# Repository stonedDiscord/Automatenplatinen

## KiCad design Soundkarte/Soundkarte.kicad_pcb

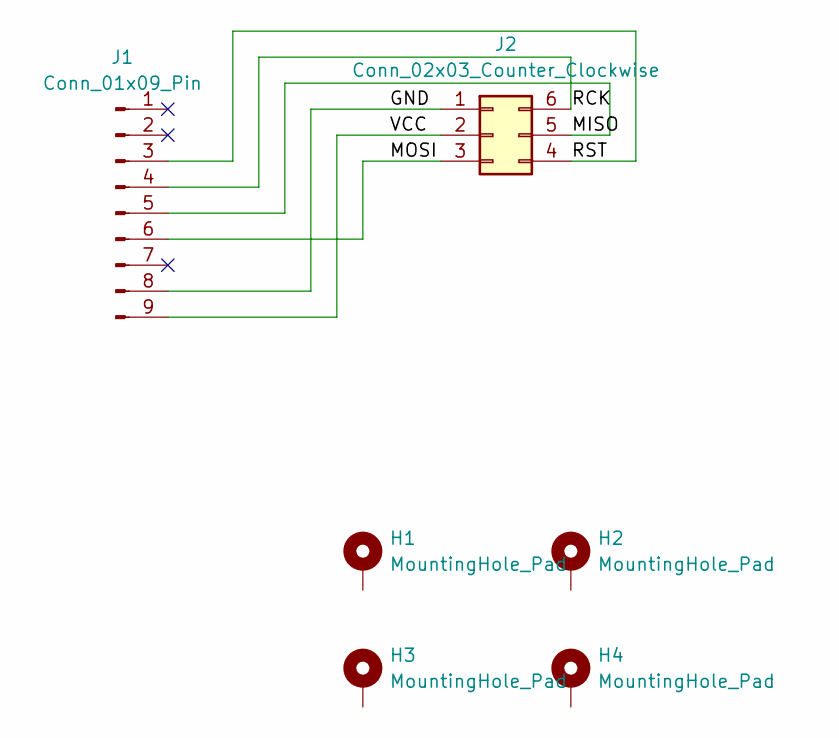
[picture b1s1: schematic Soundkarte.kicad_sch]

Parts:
H1, H2, H3, H4: MountingHole_Pad; MountingHole_4mm_Pad
J1: Conn_01x09_Pin; PinHeader_1x09_P2.54mm_Vertical
J2: Conn_02x03_Counter_Clockwise; PinHeader_2x03_P2.54mm_Vertical

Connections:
/GND: J1.8, J2.1
/MISO: J1.5, J2.5
/MOSI: J1.6, J2.3
/RCK: J1.4, J2.6
/RST: J1.3, J2.4
/VCC: J1.9, J2.2

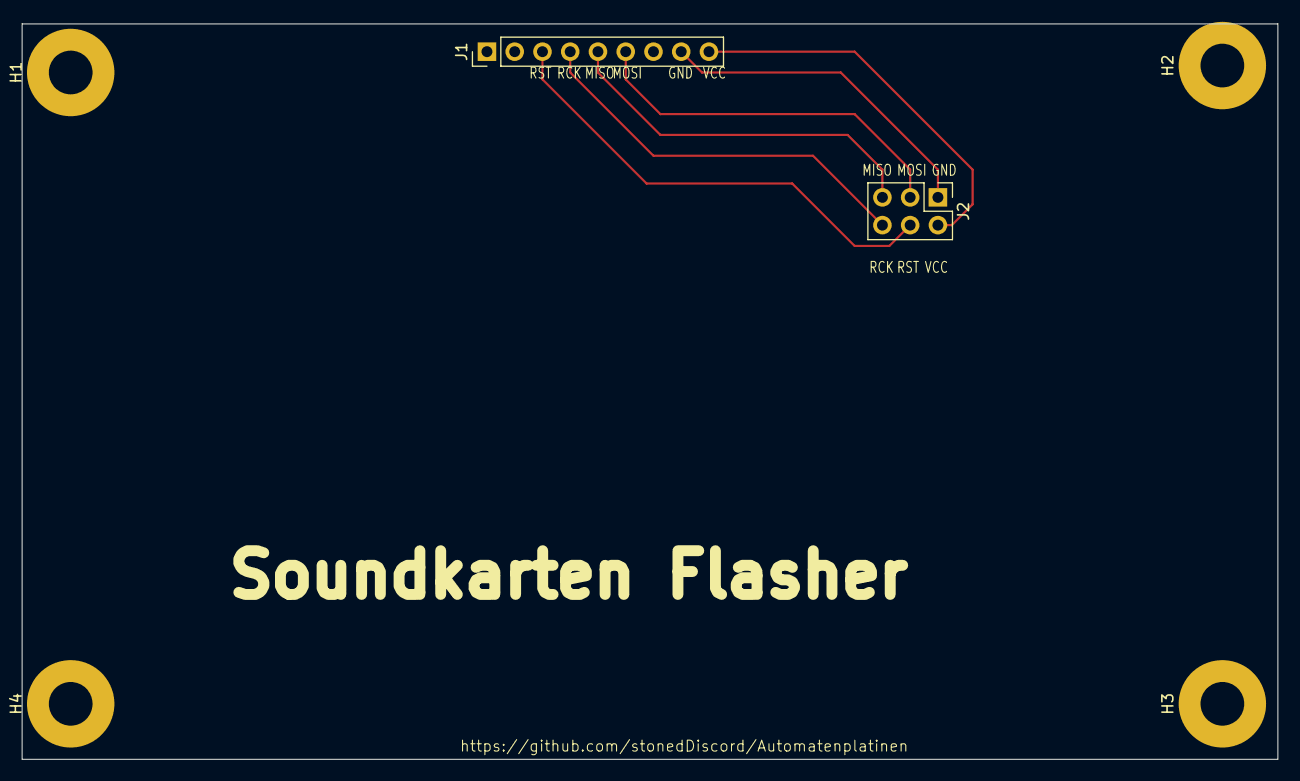
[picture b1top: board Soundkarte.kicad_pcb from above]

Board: 2 copper layers, 114.9 x 67.3 mm, 6 parts (0 on the bottom side), 6 nets.

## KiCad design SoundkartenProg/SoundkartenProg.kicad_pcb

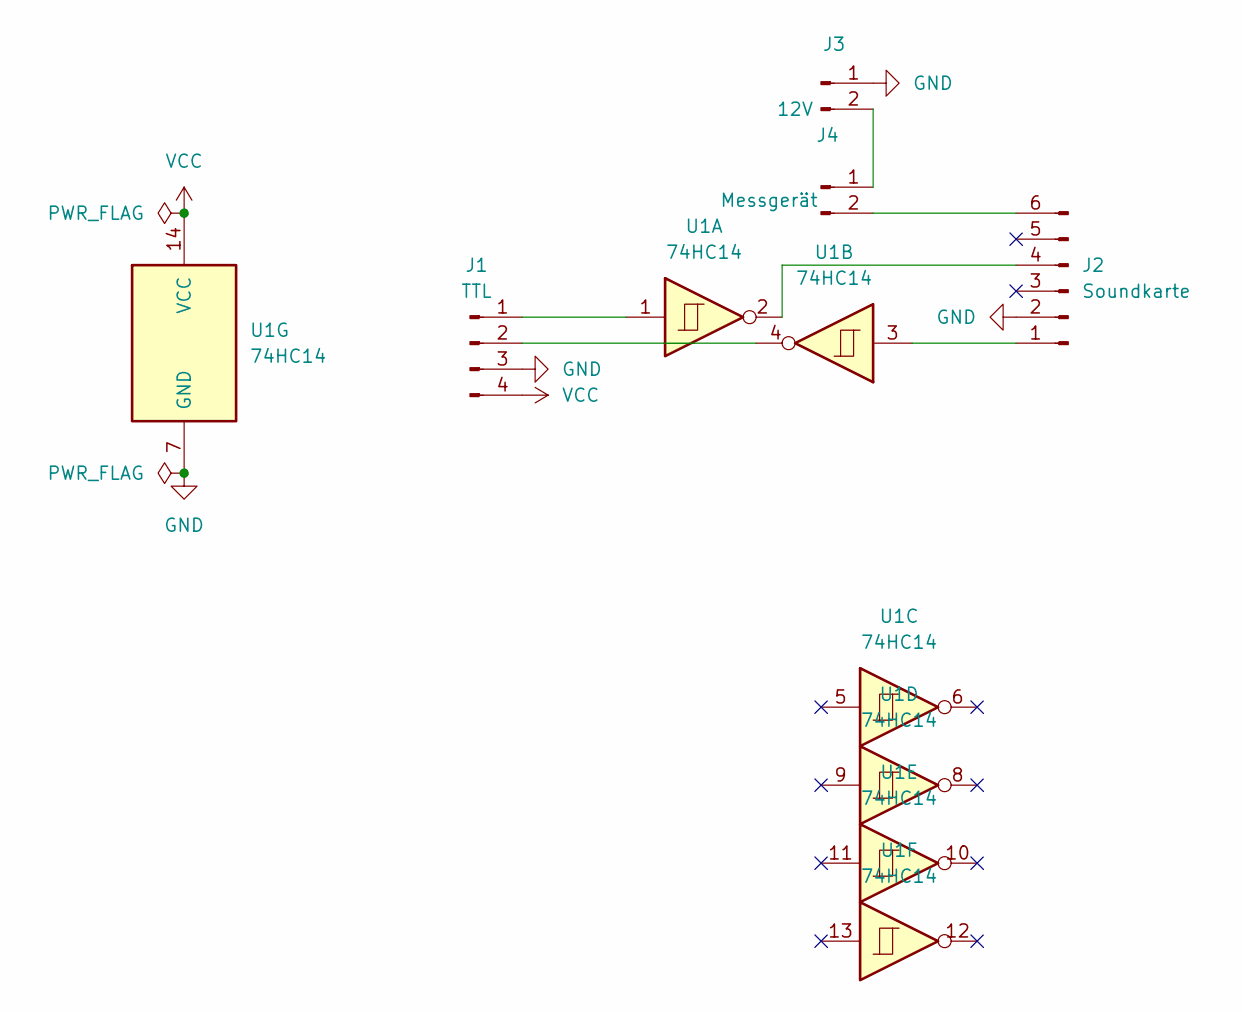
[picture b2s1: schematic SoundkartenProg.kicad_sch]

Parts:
J1: TTL; PinHeader_1x04_P2.54mm_Vertical
J2: Soundkarte; PinHeader_1x06_P2.54mm_Vertical
J3: 12V; PinHeader_1x02_P2.54mm_Vertical
J4: Messgerät; PinHeader_1x02_P2.54mm_Vertical
U1: 74HC14; SO-14_3.9x8.65mm_P1.27mm

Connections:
GND: J1.3, J2.2, J3.1, U1.7 (GND)
unnamed: J1.1, U1.1
unnamed: J1.2, U1.4
unnamed: J2.1, U1.3
unnamed: J2.4, U1.2
unnamed: J2.6, J4.2
unnamed: J3.2, J4.1
VCC: J1.4, U1.14 (VCC)

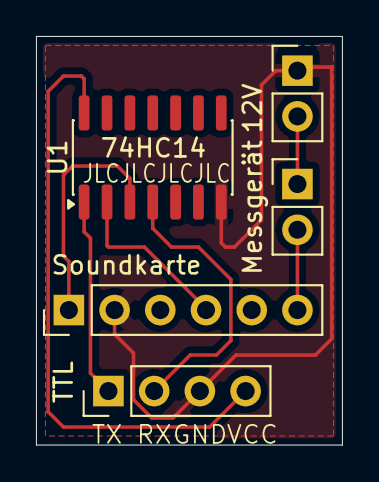
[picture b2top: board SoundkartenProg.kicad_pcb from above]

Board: 2 copper layers, 17.0 x 22.7 mm, 5 parts (0 on the bottom side), 8 nets.

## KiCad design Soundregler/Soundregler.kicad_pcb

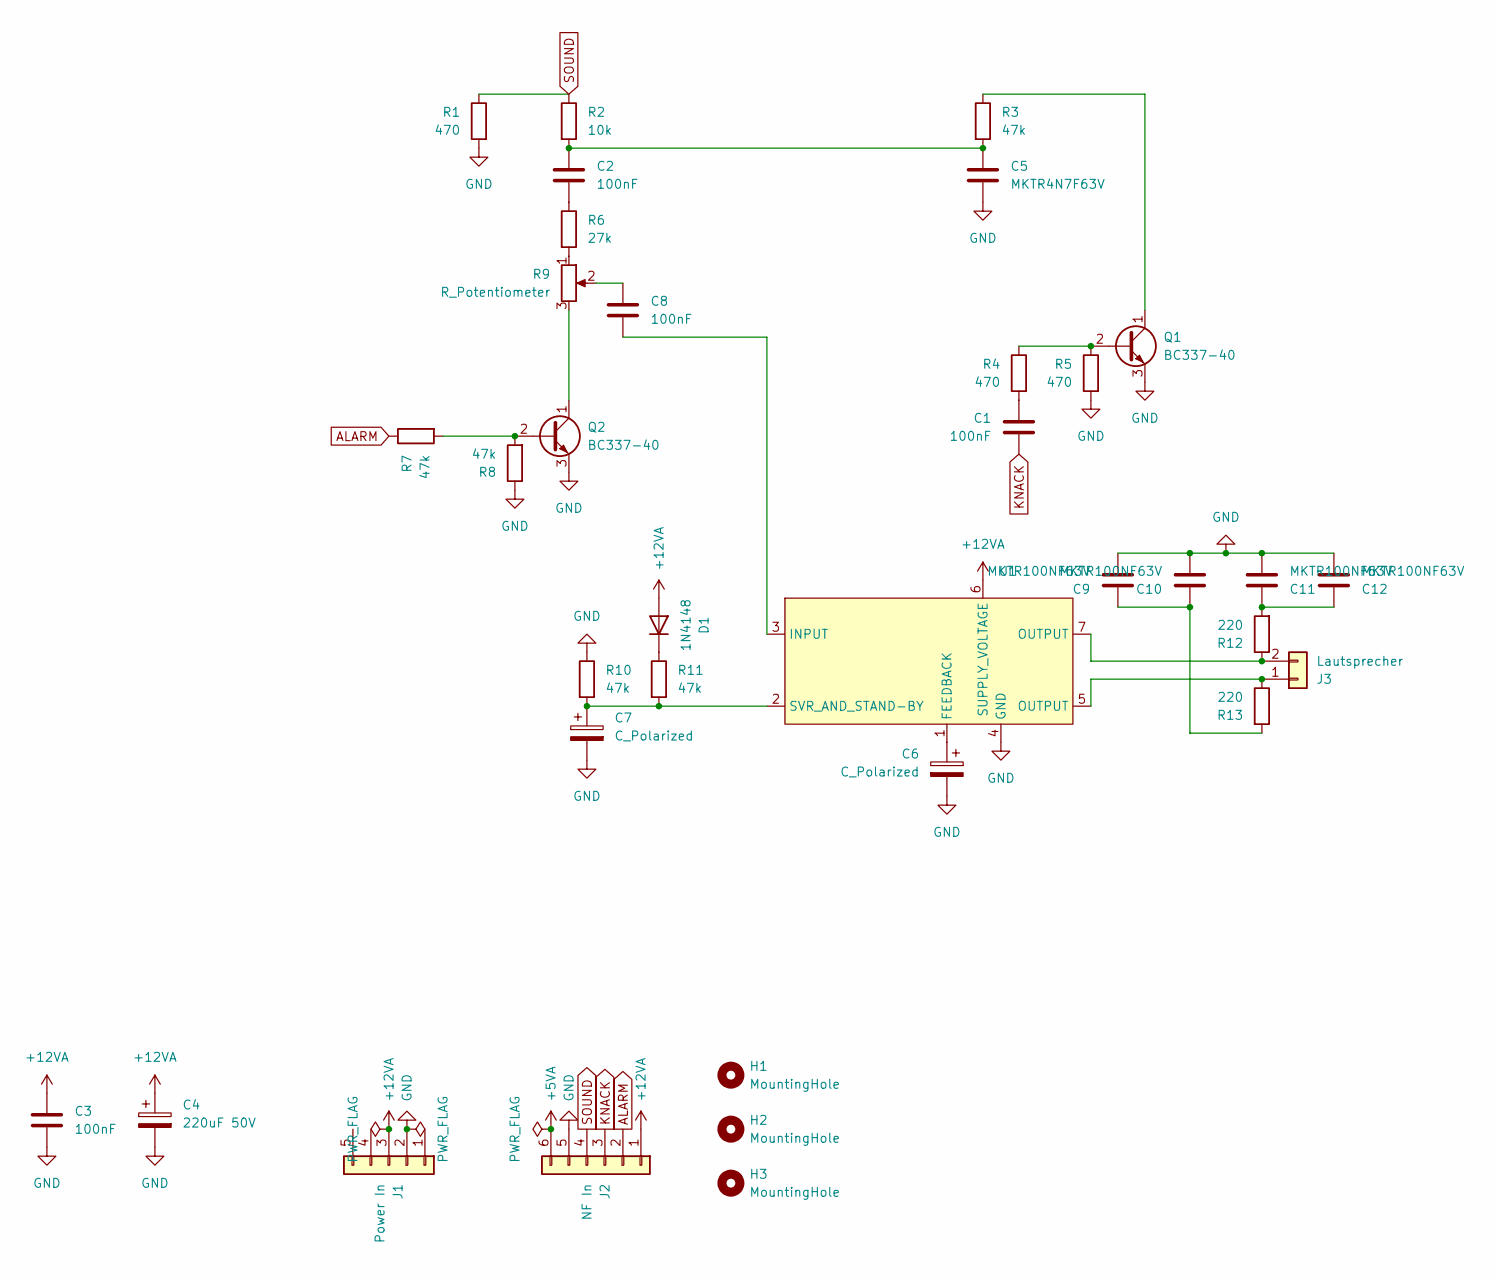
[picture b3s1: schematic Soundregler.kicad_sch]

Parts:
C1, C2, C3, C8: 100nF; C_Axial_L3.8mm_D2.6mm_P7.50mm_Horizontal
C4: 220uF 50V; CP_Radial_D8.0mm_P5.00mm
C5: MKTR4N7F63V; C_Rect_L7.0mm_W2.0mm_P5.00mm
C6, C7: C_Polarized; CP_Axial_L11.0mm_D5.0mm_P18.00mm_Horizontal
C9, C10, C11, C12: MKTR100NF63V; C_Rect_L7.0mm_W2.0mm_P5.00mm
D1: 1N4148; D_DO-35_SOD27_P7.62mm_Horizontal
H1, H2, H3: MountingHole; MountingHole_4.3mm_M4
J1: Power In; PinHeader_1x05_P2.54mm_Vertical
J2: NF In; PinHeader_1x06_P2.54mm_Vertical
J3: Lautsprecher; PinHeader_1x02_P2.54mm_Vertical
Q1, Q2: BC337-40; TO-92
R1, R4, R5: 470; R_Axial_DIN0207_L6.3mm_D2.5mm_P10.16mm_Horizontal
R2: 10k; R_Axial_DIN0207_L6.3mm_D2.5mm_P10.16mm_Horizontal
R3, R7, R8, R10, R11: 47k; R_Axial_DIN0207_L6.3mm_D2.5mm_P10.16mm_Horizontal
R6: 27k; R_Axial_DIN0207_L6.3mm_D2.5mm_P10.16mm_Horizontal
R9: R_Potentiometer; Potentiometer_ACP_CA9-V10_Vertical
R12, R13: 220; R_Axial_DIN0207_L6.3mm_D2.5mm_P10.16mm_Horizontal
U1: TO-220-7_P2.54x3.8mm_StaggerOdd_Lead5.85mm_TabDown

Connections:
+5VA: J2.6
+12VA: C3.1, C4.1, D1.2 (A), J1.3, J2.1, U1.6 (SUPPLY_VOLTAGE)
ALARM: J2.2, R7.1
GND: C3.2, C4.2, C5.2, C6.2, C7.2, C9.2, C10.2, C11.2, C12.2, J1.2, J2.5, Q1.3 (E), Q2.3 (E), R1.2, R5.2, R8.1, R10.1, U1.4 (GND)
KNACK: C1.1, J2.3
unnamed: C1.2, R4.2
unnamed: C2.1, R6.1
unnamed: C2.2, C5.1, R2.2, R3.2
unnamed: C8.1, R9.2
unnamed: C9.1, C10.1, R13.2
unnamed: C11.1, C12.1, R12.2
unnamed: D1.1 (K), R11.1
unnamed: J3.1, R13.1, U1.5 (OUTPUT)
unnamed: J3.2, R12.1, U1.7 (OUTPUT)
unnamed: Q1.2 (B), R4.1, R5.1
unnamed: Q1.1 (C), R3.1
unnamed: Q2.2 (B), R7.2, R8.2
unnamed: Q2.1 (C), R9.3
unnamed: R6.2, R9.1
unnamed: C6.1, U1.1 (FEEDBACK)
unnamed: C8.2, U1.3 (INPUT)
unnamed: C7.1, R10.2, R11.2, U1.2 (SVR_AND_STAND-BY)
SOUND: J2.4, R1.1, R2.1

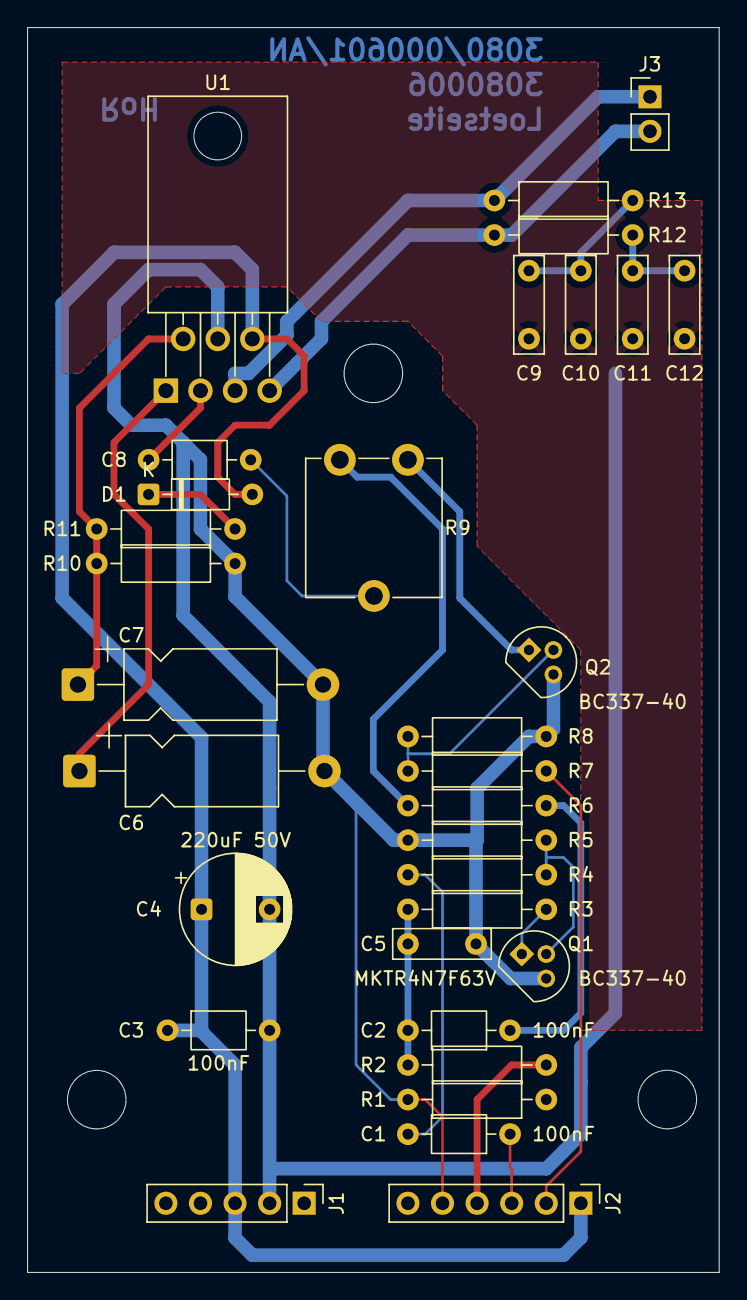
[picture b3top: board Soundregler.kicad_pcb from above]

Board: 2 copper layers, 50.8 x 91.4 mm, 35 parts (0 on the bottom side), 22 nets.

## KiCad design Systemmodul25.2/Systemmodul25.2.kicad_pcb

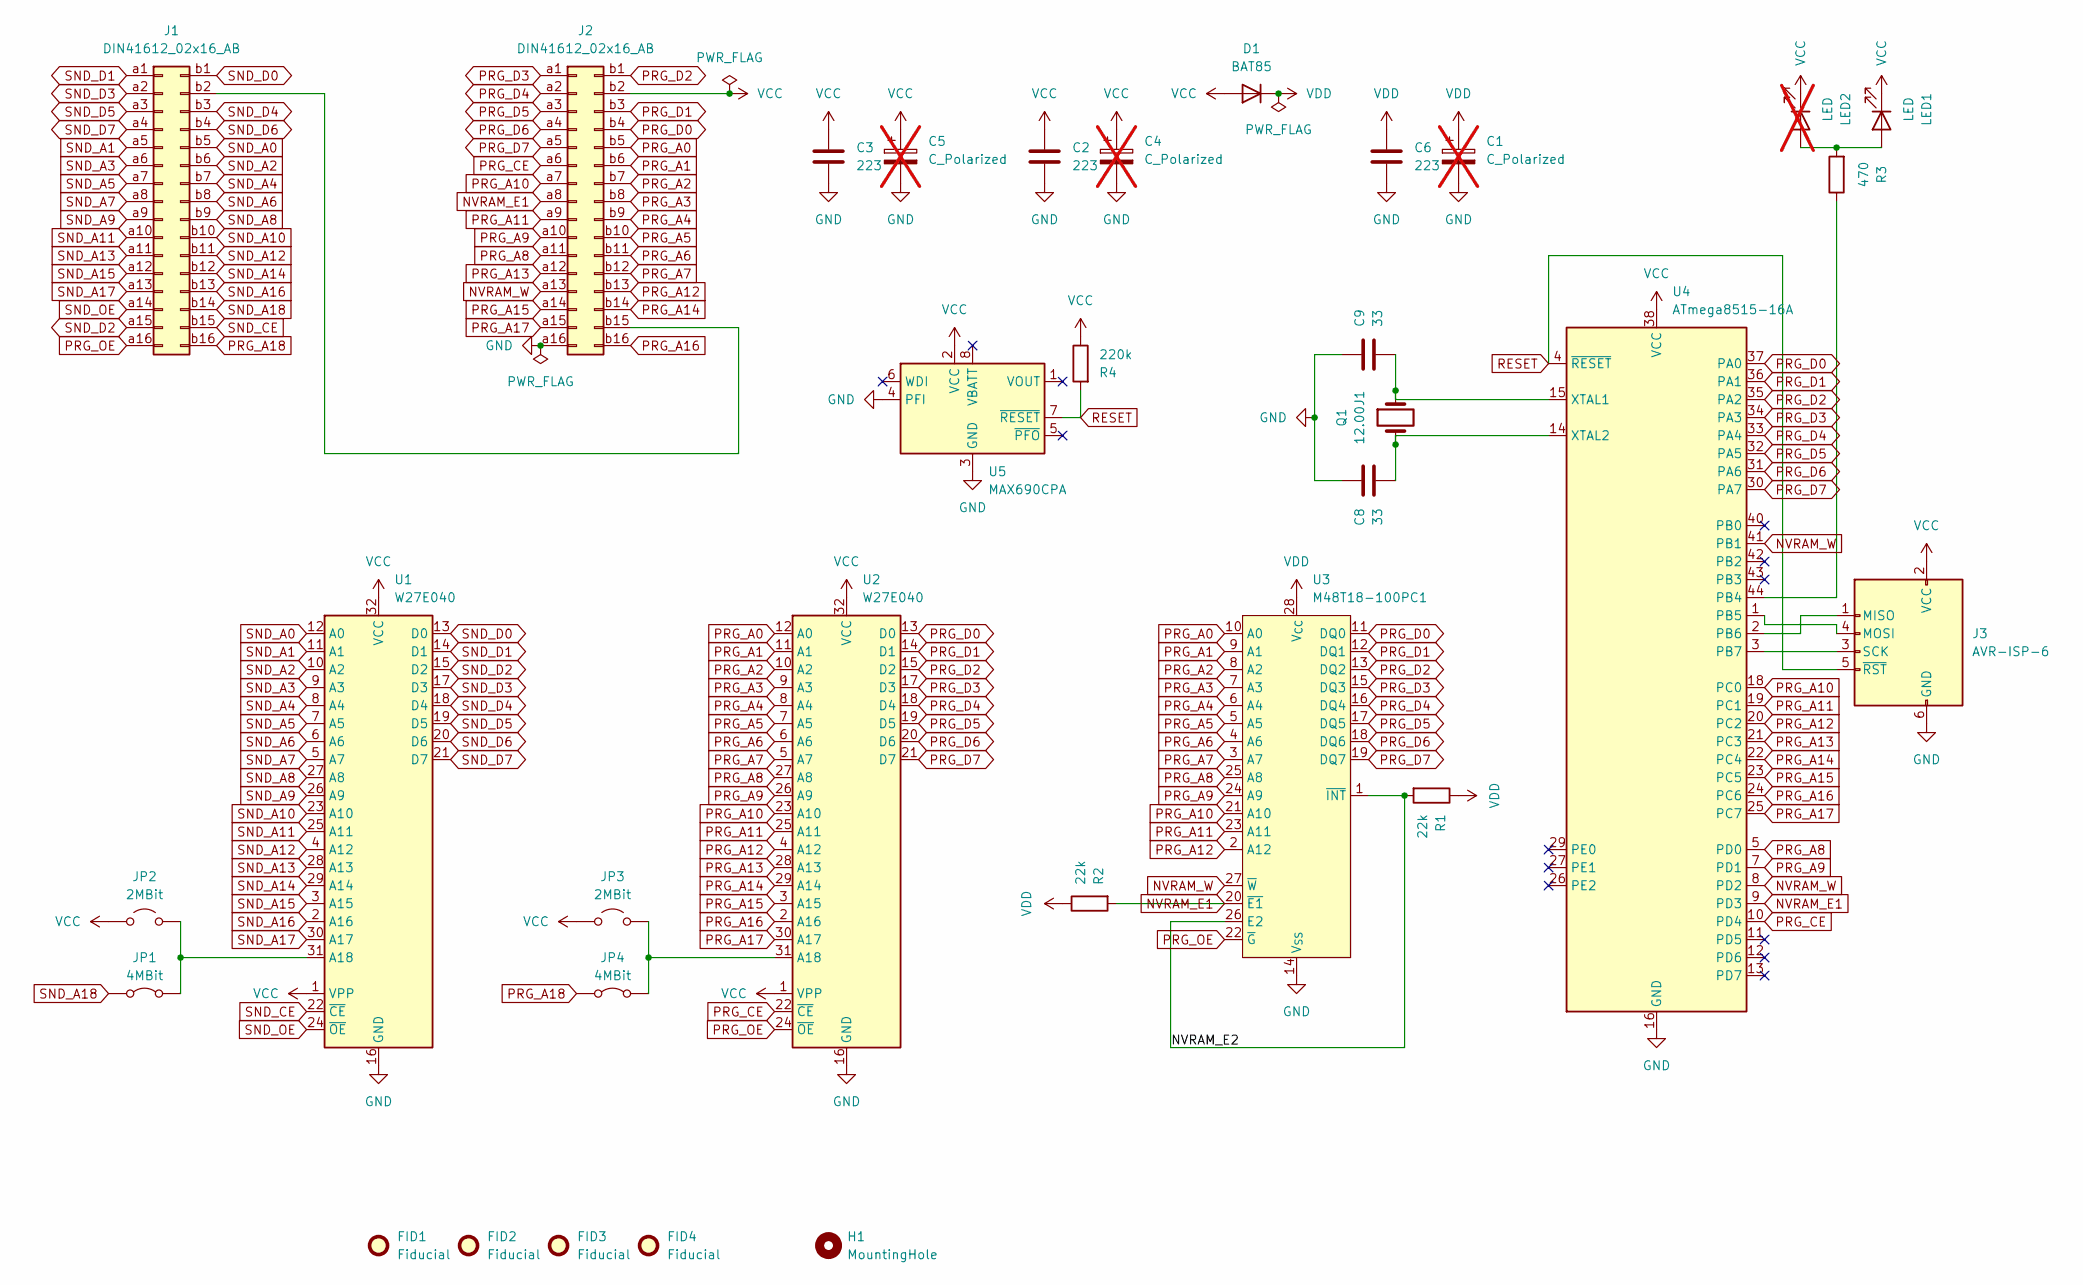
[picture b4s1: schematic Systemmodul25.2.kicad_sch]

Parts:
C1: C_Polarized; CP_Radial_Tantal_D7.0mm_P5.00mm; not fitted
C2, C3, C6: 223; C_Disc_D4.3mm_W1.9mm_P5.00mm
C4, C5: C_Polarized; CP_Radial_Tantal_D5.0mm_P5.00mm; not fitted
C8, C9: 33; C_Disc_D4.3mm_W1.9mm_P5.00mm
D1: BAT85; D_A-405_P10.16mm_Horizontal
FID1, FID2: Fiducial; Fiducial_Cross_1.5mm_Mask2mm
FID3: Fiducial; Fiducial_0.75mm_Mask1.5mm
FID4: Fiducial; Fiducial_0.5mm_Mask1mm
H1: MountingHole; MountingHole_4.3mm_M4
J1, J2: DIN41612_02x16_AB; DIN41612_Q2_2x16_Male_Vertical_THT
J3: AVR-ISP-6; IDC-Header_2x03_P2.54mm_Vertical
JP1, JP4: 4MBit; NSM_Jumper
JP2, JP3: 2MBit; NSM_Jumper
LED1: LED; LED_D5.0mm_Horizontal_O1.27mm_Z3.0mm
LED2: LED; LED_1206_3216Metric; not fitted
Q1: 12.00J1; Crystal_HC18-U_Vertical
R1, R2: 22k; R_Axial_DIN0207_L6.3mm_D2.5mm_P10.16mm_Horizontal
R3: 470; R_Axial_DIN0207_L6.3mm_D2.5mm_P10.16mm_Horizontal
R4: 220k; R_Axial_DIN0207_L6.3mm_D2.5mm_P10.16mm_Horizontal
U1, U2: W27E040; DIP-32_W15.24mm_Socket
U3: M48T18-100PC1; DIP-28_W15.24mm
U4: ATmega8515-16A; TQFP-44_10x10mm_P0.8mm
U5: MAX690CPA; DIP-8_W7.62mm

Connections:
/NVRAM_E2: R1.2, U3.1 (~INT), U3.26 (E2)
GND: C1.2, C2.2, C3.2, C4.2, C5.2, C6.2, C8.1, C9.1, J2.a16, J3.6 (GND), U1.16 (GND), U2.16 (GND), U3.14 (V_{SS}), U4.16 (GND), U5.3 (GND), U5.4 (PFI)
NVRAM_E1: J2.a8, R2.2, U3.20 (~E1), U4.9 (PD3)
NVRAM_W: J2.a13, U3.27 (~W), U4.8 (PD2), U4.41 (PB1)
unnamed: J1.b2, J2.b15
unnamed: J3.1 (MISO), U4.2 (PB6)
unnamed: J3.4 (MOSI), U4.1 (PB5)
unnamed: J3.3 (SCK), U4.3 (PB7)
unnamed: JP1.1 (A), JP2.1 (A), U1.31 (A18)
unnamed: JP3.1 (A), JP4.1 (A), U2.31 (A18)
unnamed: LED1.2 (A), LED2.2 (A), R3.2
unnamed: R3.1, U4.44 (PB4)
unnamed: C9.2, Q1.1, U4.15 (XTAL1)
unnamed: C8.2, Q1.2, U4.14 (XTAL2)
PRG_A0: J2.b5, U2.12 (A0), U3.10 (A0)
PRG_A1: J2.b6, U2.11 (A1), U3.9 (A1)
PRG_A2: J2.b7, U2.10 (A2), U3.8 (A2)
PRG_A3: J2.b8, U2.9 (A3), U3.7 (A3)
PRG_A4: J2.b9, U2.8 (A4), U3.6 (A4)
PRG_A5: J2.b10, U2.7 (A5), U3.5 (A5)
PRG_A6: J2.b11, U2.6 (A6), U3.4 (A6)
PRG_A7: J2.b12, U2.5 (A7), U3.3 (A7)
PRG_A8: J2.a11, U2.27 (A8), U3.25 (A8), U4.5 (PD0)
PRG_A9: J2.a10, U2.26 (A9), U3.24 (A9), U4.7 (PD1)
PRG_A10: J2.a7, U2.23 (A10), U3.21 (A10), U4.18 (PC0)
PRG_A11: J2.a9, U2.25 (A11), U3.23 (A11), U4.19 (PC1)
PRG_A12: J2.b13, U2.4 (A12), U3.2 (A12), U4.20 (PC2)
PRG_A13: J2.a12, U2.28 (A13), U4.21 (PC3)
PRG_A14: J2.b14, U2.29 (A14), U4.22 (PC4)
PRG_A15: J2.a14, U2.3 (A15), U4.23 (PC5)
PRG_A16: J2.b16, U2.2 (A16), U4.24 (PC6)
PRG_A17: J2.a15, U2.30 (A17), U4.25 (PC7)
PRG_A18: J1.b16, JP4.2 (B)
PRG_CE: J2.a6, U2.22 (~CE), U4.10 (PD4)
PRG_D0: J2.b4, U2.13 (D0), U3.11 (DQ0), U4.37 (PA0)
PRG_D1: J2.b3, U2.14 (D1), U3.12 (DQ1), U4.36 (PA1)
PRG_D2: J2.b1, U2.15 (D2), U3.13 (DQ2), U4.35 (PA2)
PRG_D3: J2.a1, U2.17 (D3), U3.15 (DQ3), U4.34 (PA3)
PRG_D4: J2.a2, U2.18 (D4), U3.16 (DQ4), U4.33 (PA4)
PRG_D5: J2.a3, U2.19 (D5), U3.17 (DQ5), U4.32 (PA5)
PRG_D6: J2.a4, U2.20 (D6), U3.18 (DQ6), U4.31 (PA6)
PRG_D7: J2.a5, U2.21 (D7), U3.19 (DQ7), U4.30 (PA7)
PRG_OE: J1.a16, U2.24 (~OE), U3.22 (~G)
RESET: J3.5 (~RST), R4.2, U4.4 (~RESET), U5.7 (~RESET)
SND_A0: J1.b5, U1.12 (A0)
SND_A1: J1.a5, U1.11 (A1)
SND_A2: J1.b6, U1.10 (A2)
SND_A3: J1.a6, U1.9 (A3)
SND_A4: J1.b7, U1.8 (A4)
SND_A5: J1.a7, U1.7 (A5)
SND_A6: J1.b8, U1.6 (A6)
SND_A7: J1.a8, U1.5 (A7)
SND_A8: J1.b9, U1.27 (A8)
SND_A9: J1.a9, U1.26 (A9)
SND_A10: J1.b10, U1.23 (A10)
SND_A11: J1.a10, U1.25 (A11)
SND_A12: J1.b11, U1.4 (A12)
SND_A13: J1.a11, U1.28 (A13)
SND_A14: J1.b12, U1.29 (A14)
SND_A15: J1.a12, U1.3 (A15)
SND_A16: J1.b13, U1.2 (A16)
SND_A17: J1.a13, U1.30 (A17)
SND_A18: J1.b14, JP1.2 (B)
SND_CE: J1.b15, U1.22 (~CE)
SND_D0: J1.b1, U1.13 (D0)
SND_D1: J1.a1, U1.14 (D1)
SND_D2: J1.a15, U1.15 (D2)
SND_D3: J1.a2, U1.17 (D3)
SND_D4: J1.b3, U1.18 (D4)
SND_D5: J1.a3, U1.19 (D5)
SND_D6: J1.b4, U1.20 (D6)
SND_D7: J1.a4, U1.21 (D7)
SND_OE: J1.a14, U1.24 (~OE)
VCC: C2.1, C3.1, C4.1, C5.1, D1.2 (A), J2.b2, J3.2 (VCC), JP2.2 (B), JP3.2 (B), LED1.1 (K), LED2.1 (K), R4.1, U1.1 (VPP), U1.32 (VCC), U2.1 (VPP), U2.32 (VCC), U4.38 (VCC), U5.2 (VCC)
VDD: C1.1, C6.1, D1.1 (K), R1.1, R2.1, U3.28 (V_{CC})

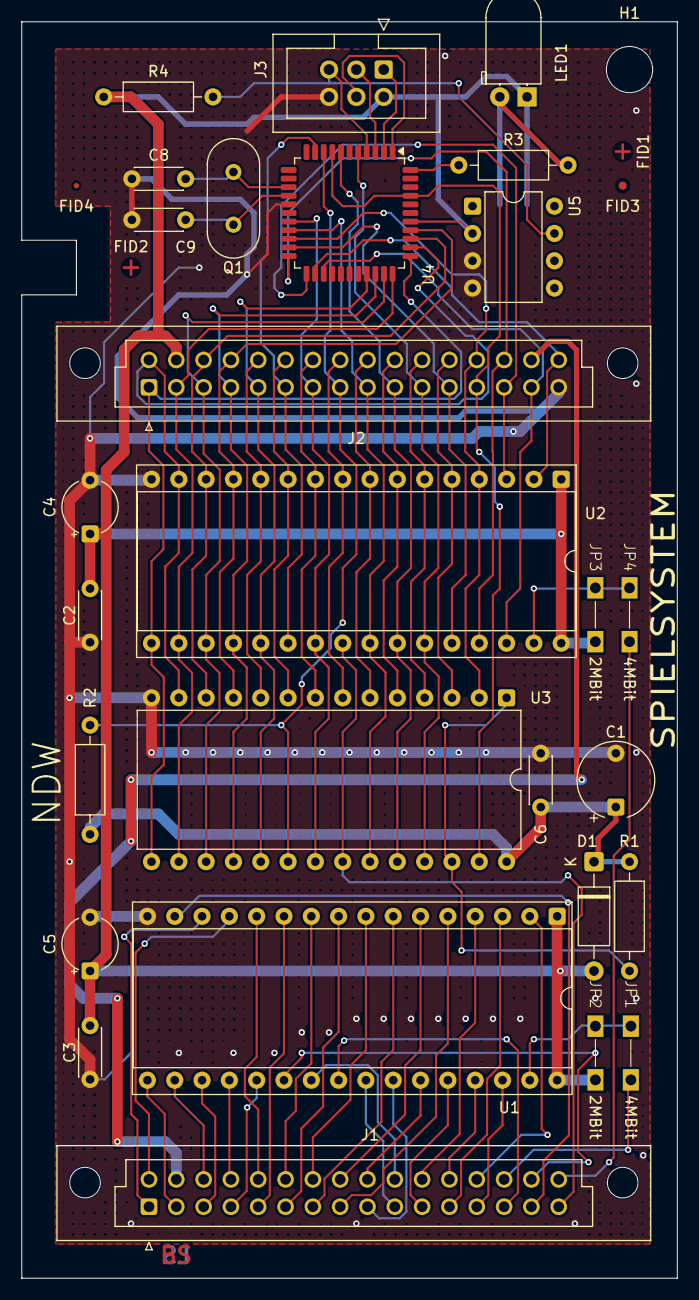
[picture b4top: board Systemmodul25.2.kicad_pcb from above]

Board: 2 copper layers, 61.0 x 116.8 mm, 33 parts (1 on the bottom side), 75 nets.

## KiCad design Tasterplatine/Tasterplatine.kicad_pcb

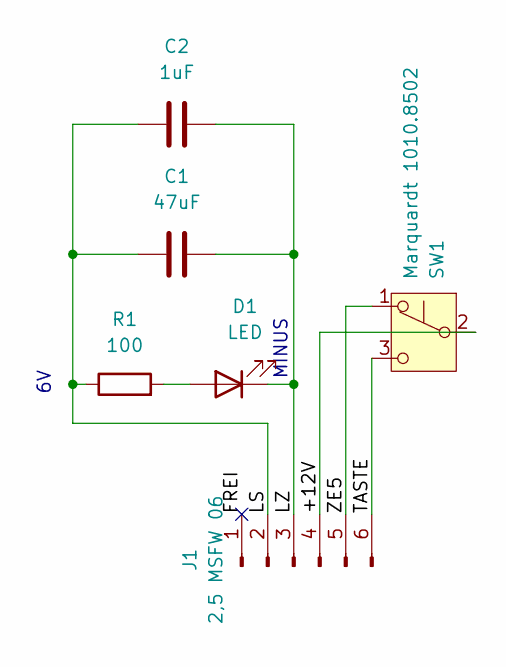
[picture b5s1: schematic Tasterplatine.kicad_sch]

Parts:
C1: 47uF; CP_EIA-3528-12_Kemet-T
C2: 1uF; C_1206_3216Metric
D1: LED; LED_PLCC_2835_Handsoldering
J1: 2,5 MSFW 06; JST_EH_S6B-EH_1x06_P2.50mm_Horizontal
R1: 100; R_1206_3216Metric
SW1: Marquardt 1010.8502; Marquardt1010

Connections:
/+12V: J1.4, SW1.2 (B)
/FREI: J1.1
/LS: C1.1, C2.1, J1.2, R1.1
/LZ: C1.2, C2.2, D1.1 (K), J1.3
/TASTE: J1.6, SW1.3 (C)
/ZE5: J1.5, SW1.1 (A)
unnamed: D1.2 (A), R1.2

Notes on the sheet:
MINUS

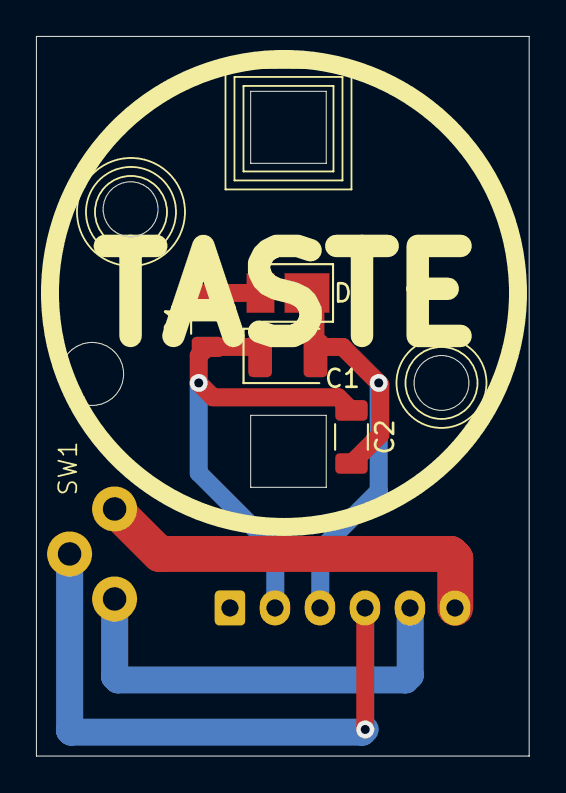
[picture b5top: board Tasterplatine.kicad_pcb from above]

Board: 2 copper layers, 27.4 x 40.0 mm, 6 parts (1 on the bottom side), 6 nets.

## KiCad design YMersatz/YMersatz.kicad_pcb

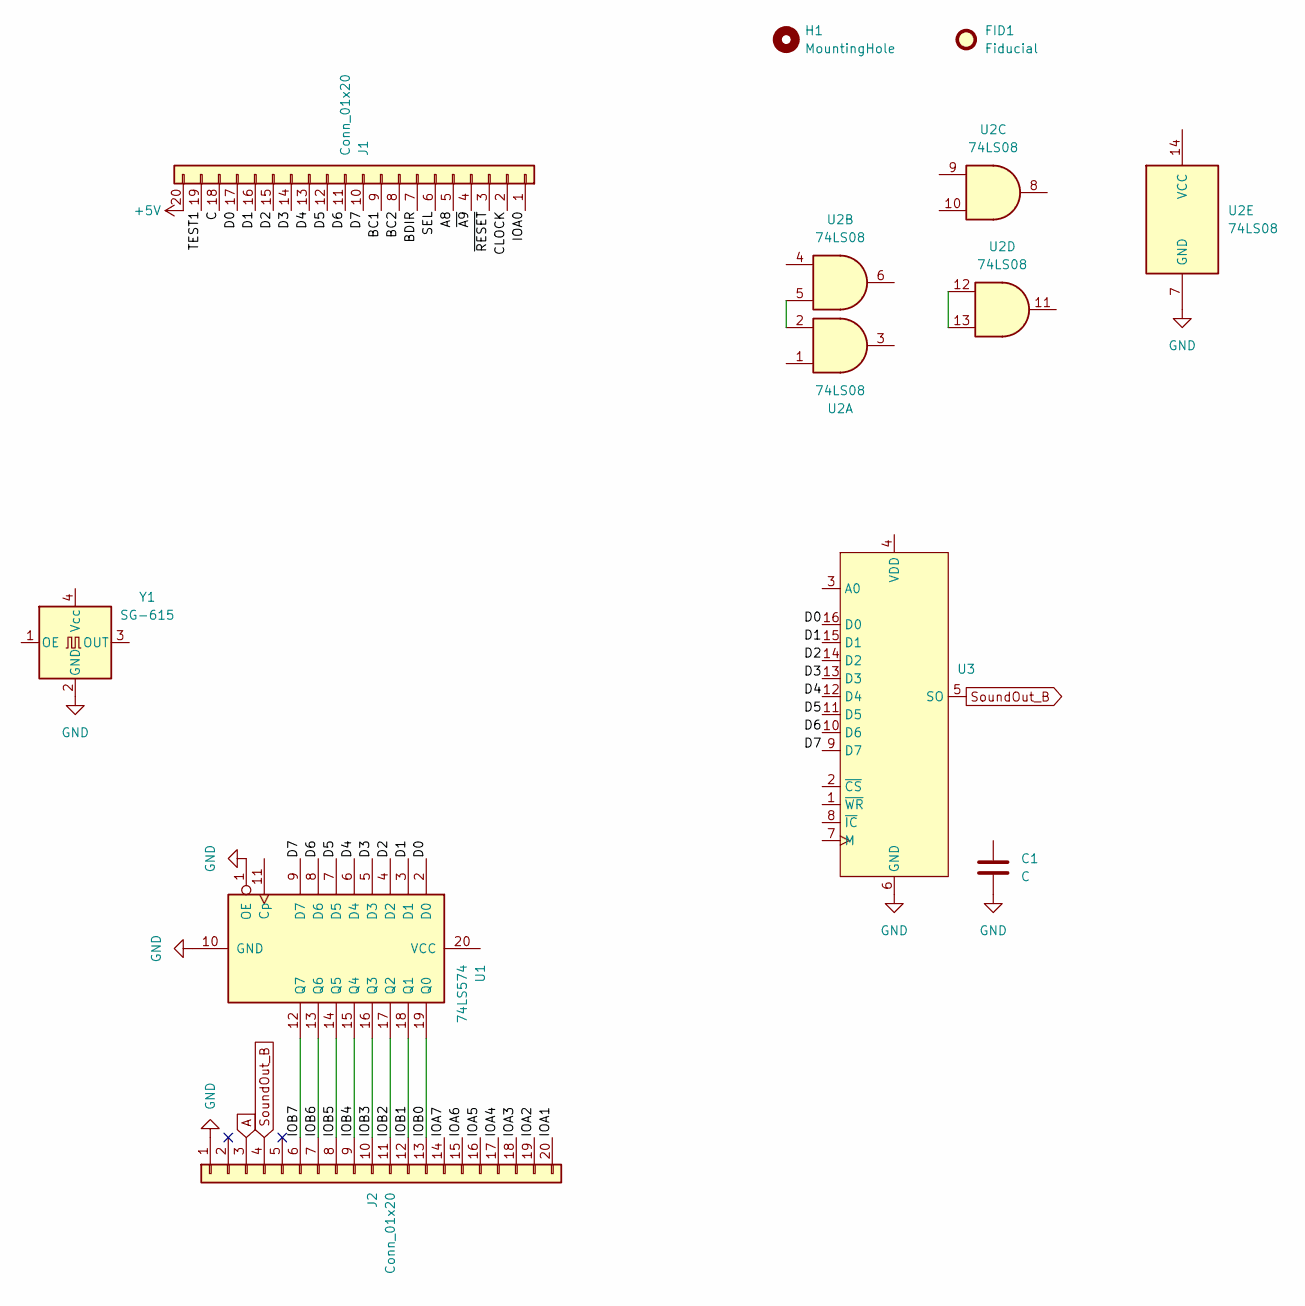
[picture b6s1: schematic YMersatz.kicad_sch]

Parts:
C1: C; C_0805_2012Metric
FID1: Fiducial; Fiducial_1.5mm_Mask3mm
H1: MountingHole; MountingHole_2.1mm
J1, J2: Conn_01x20; PinHeader_1x20_P2.54mm_Vertical
U1: 74LS574; SO-20_12.8x7.5mm_P1.27mm
U2: 74LS08; SO-14_3.9x8.65mm_P1.27mm
U3: SO-16_5.3x10.2mm_P1.27mm
Y1: SG-615; Oscillator_SMD_SeikoEpson_SG8002JA-4Pin_14.0x8.7mm

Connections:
+5V: J1.20
/A8: J1.5
/BC1: J1.9
/BC2: J1.8
/BDIR: J1.7
/C: J1.18
/CLOCK: J1.2
/D0: J1.17, U1.2 (D0), U3.16 (D0)
/D1: J1.16, U1.3 (D1), U3.15 (D1)
/D2: J1.15, U1.4 (D2), U3.14 (D2)
/D3: J1.14, U1.5 (D3), U3.13 (D3)
/D4: J1.13, U1.6 (D4), U3.12 (D4)
/D5: J1.12, U1.7 (D5), U3.11 (D5)
/D6: J1.11, U1.8 (D6), U3.10 (D6)
/D7: J1.10, U1.9 (D7), U3.9 (D7)
/IOA0: J1.1
/IOA1: J2.20
/IOA2: J2.19
/IOA3: J2.18
/IOA4: J2.17
/IOA5: J2.16
/IOA6: J2.15
/IOA7: J2.14
/IOB0: J2.13, U1.19 (Q0)
/IOB1: J2.12, U1.18 (Q1)
/IOB2: J2.11, U1.17 (Q2)
/IOB3: J2.10, U1.16 (Q3)
/IOB4: J2.9, U1.15 (Q4)
/IOB5: J2.8, U1.14 (Q5)
/IOB6: J2.7, U1.13 (Q6)
/IOB7: J2.6, U1.12 (Q7)
/SEL: J1.6
/TEST1: J1.19
/~A9: J1.4
/~RESET: J1.3
A: J2.3
GND: C1.2, J2.1, U1.1 (OE), U1.10 (GND), U2.7 (GND_7), U3.6 (GND), Y1.2 (GND_2)
unnamed: U2.2, U2.5
unnamed: U2.12, U2.13
SoundOut_B: J2.4, U3.5 (SO)

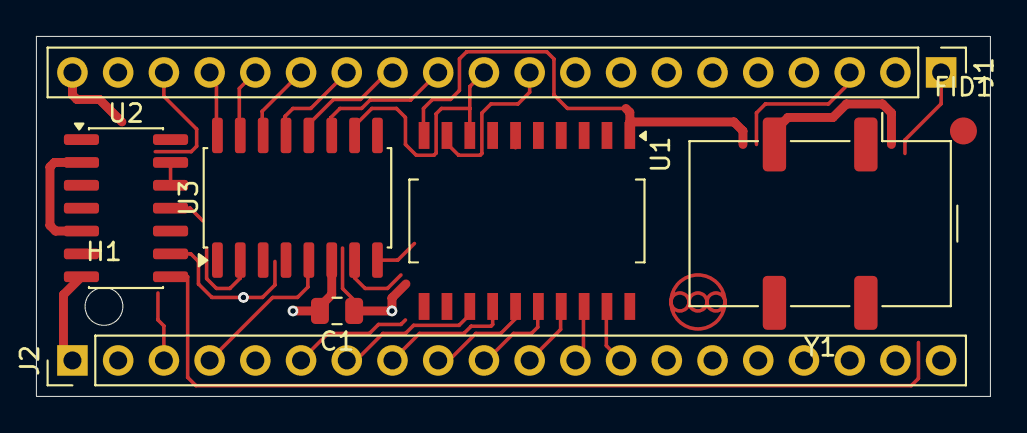
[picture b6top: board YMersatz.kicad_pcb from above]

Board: 2 copper layers, 53.0 x 20.0 mm, 9 parts (0 on the bottom side), 20 nets.

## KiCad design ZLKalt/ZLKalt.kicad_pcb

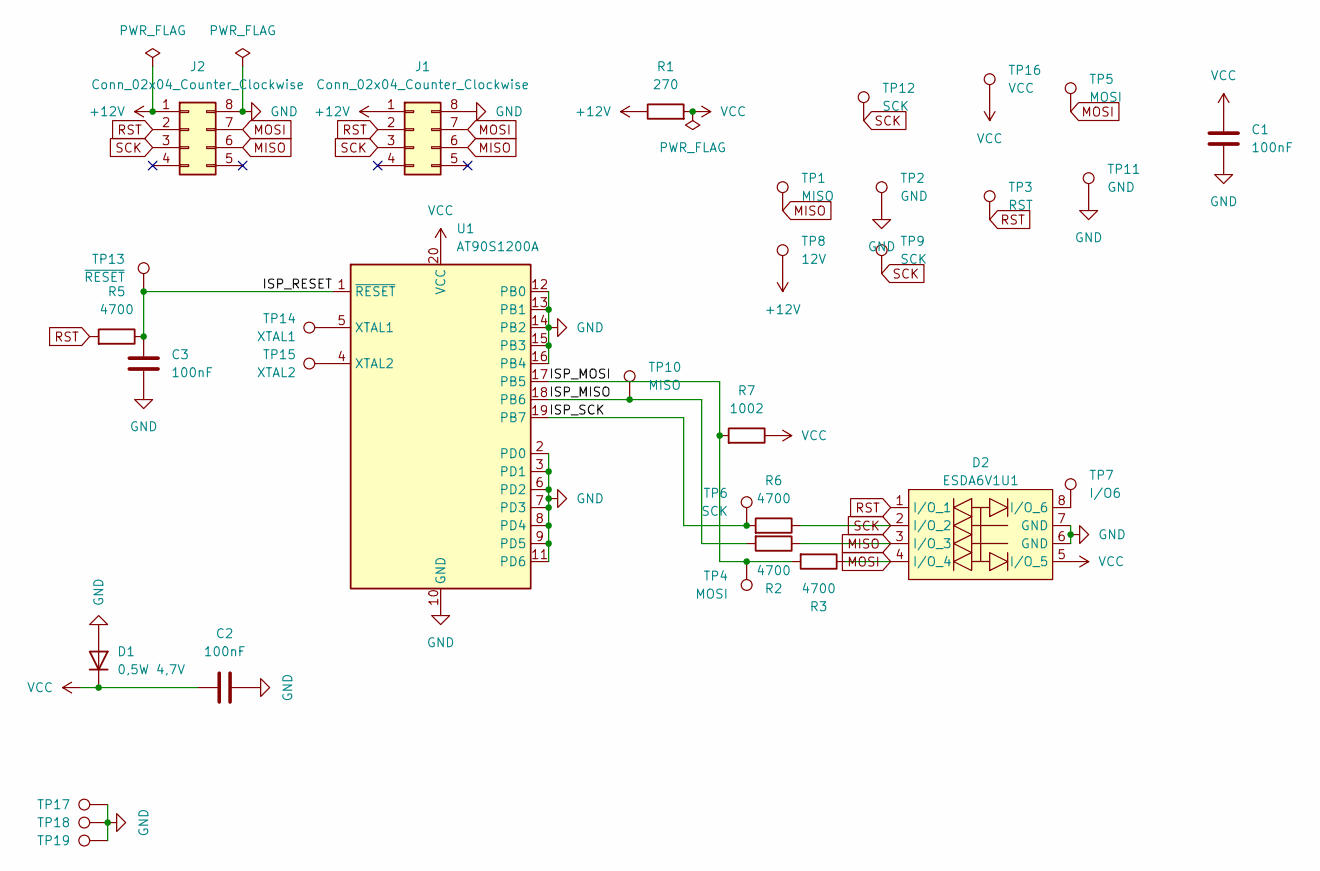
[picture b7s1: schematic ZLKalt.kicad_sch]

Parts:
C1, C2, C3: 100nF; C_0805_2012Metric_Pad1.18x1.45mm_HandSolder
D1: 0,5W 4,7V; D_1206_3216Metric
D2: ESDA6V1U1; SO-8_3.9x4.9mm_P1.27mm
J1, J2: Conn_02x04_Counter_Clockwise; ZLK
R1: 270; R_0603_1608Metric
R2, R3, R5, R6: 4700; R_0603_1608Metric
R7: 1002; R_0603_1608Metric
TP1, TP10: MISO; TestPoint_Pad_D1.5mm
TP2, TP11: GND; TestPoint_Pad_D1.5mm
TP3: RST; TestPoint_Pad_D1.5mm
TP4, TP5: MOSI; TestPoint_Pad_D1.5mm
TP6, TP9, TP12: SCK; TestPoint_Pad_D1.5mm
TP7: I/O6; TestPoint_Pad_D1.5mm
TP8: 12V; TestPoint_Pad_D1.5mm
TP13: ~{RESET}; TestPoint_Pad_D1.5mm
TP14: XTAL1; TestPoint_Pad_D1.5mm
TP15: XTAL2; TestPoint_Pad_D1.5mm
TP16: VCC; TestPoint_Pad_D1.5mm
TP17, TP18, TP19: TestPoint; TestPoint_THTPad_D2.0mm_Drill1.0mm
U1: AT90S1200A; SOP-20_7.5x12.8mm_P1.27mm

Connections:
+12V: J1.1, J2.1, R1.1, TP8.1
/ISP_MISO: R2.2, TP10.1, U1.18 (PB6)
/ISP_MOSI: R3.2, R7.2, TP4.1, U1.17 (PB5)
/ISP_RESET: C3.1, R5.1, TP13.1, U1.1 (~RESET)
/ISP_SCK: R6.2, TP6.1, U1.19 (PB7)
GND: C1.2, C2.2, C3.2, D1.2 (A), D2.6 (GND), D2.7 (GND), J1.8, J2.8, TP2.1, TP11.1, TP17.1, TP18.1, TP19.1, U1.2 (PD0), U1.3 (PD1), U1.6 (PD2), U1.7 (PD3), U1.8 (PD4), U1.9 (PD5), U1.10 (GND), U1.11 (PD6), U1.12 (PB0), U1.13 (PB1), U1.14 (PB2), U1.15 (PB3), U1.16 (PB4)
MISO: D2.3 (I/O_3), J1.6, J2.6, R2.1, TP1.1
MOSI: D2.4 (I/O_4), J1.7, J2.7, R3.1, TP5.1
unnamed: D2.8 (I/O_6), TP7.1
unnamed: TP14.1, U1.5 (XTAL1)
unnamed: TP15.1, U1.4 (XTAL2)
RST: D2.1 (I/O_1), J1.2, J2.2, R5.2, TP3.1
SCK: D2.2 (I/O_2), J1.3, J2.3, R6.1, TP9.1, TP12.1
VCC: C1.1, C2.1, D1.1 (K), D2.5 (I/O_5), R1.2, R7.1, TP16.1, U1.20 (VCC)

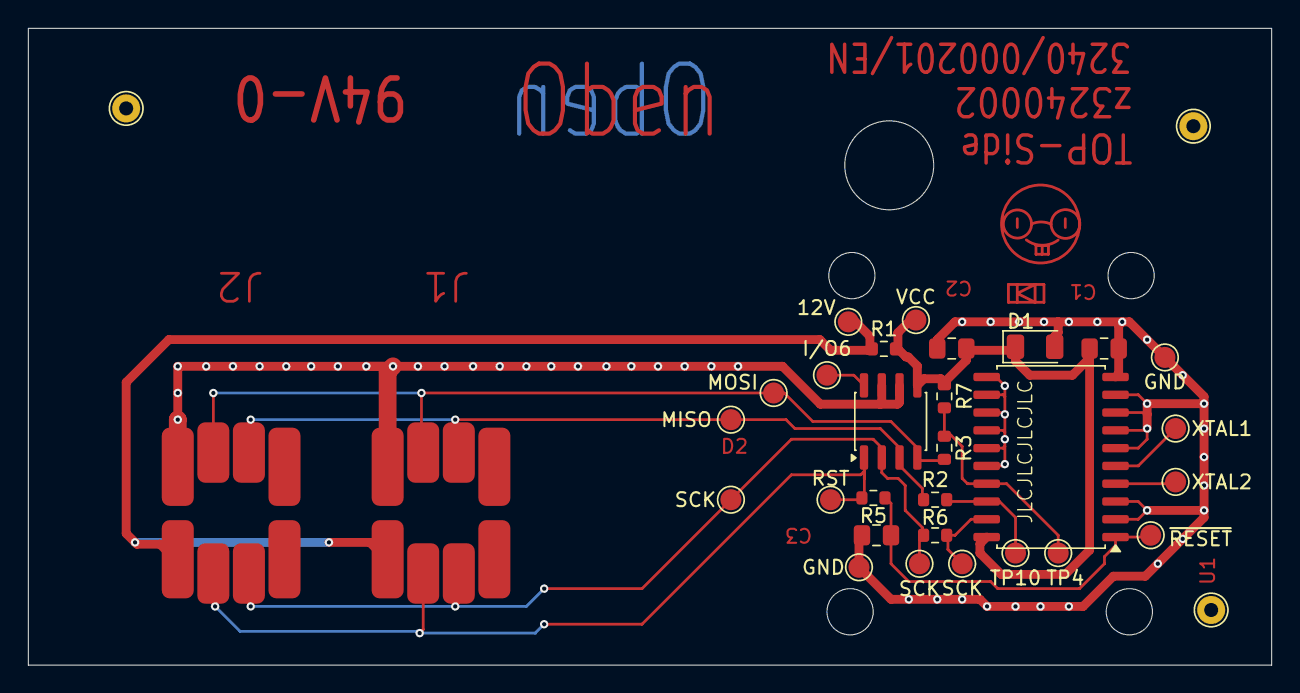
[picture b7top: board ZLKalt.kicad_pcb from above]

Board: 2 copper layers, 88.8 x 45.5 mm, 33 parts (0 on the bottom side), 14 nets.
